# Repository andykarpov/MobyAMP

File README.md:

This project is a hobbyst DIY 2.1 amplifier based on TDA2030A and TDA1557Q chips.

The heart of the project is an arduino compatible custom board called "interface board" 
with atmega328 microcontroller and 16x2 (or 20x4) LCD panel, encoder, resistive keyboard and audio processor PT2322.
It is possible to make it even on a breadboard using a standard arduino and couple of wires :)

Some basic boards, such as interface board and amp boards contains both pcb design and electrical schematics.
All drawing (build/pdfs/pngs/etc) are already prepared to be printed on transarent sheets to make a final PCBs 
from the presensitized PCBs at home.

A few other things are not yet described (such as power board, connection between modules, etc, etc).
To be continued...

Custom eagle libraries are located under eagle_libraries folder.
To make a gerber / images from the command line you must have:
1. OSX (could work on other UNIX/Linux boxes)
2. eagle
3. homebrew
4. gerbv

Scripts should be changed to reflect a current Eagle installation path.

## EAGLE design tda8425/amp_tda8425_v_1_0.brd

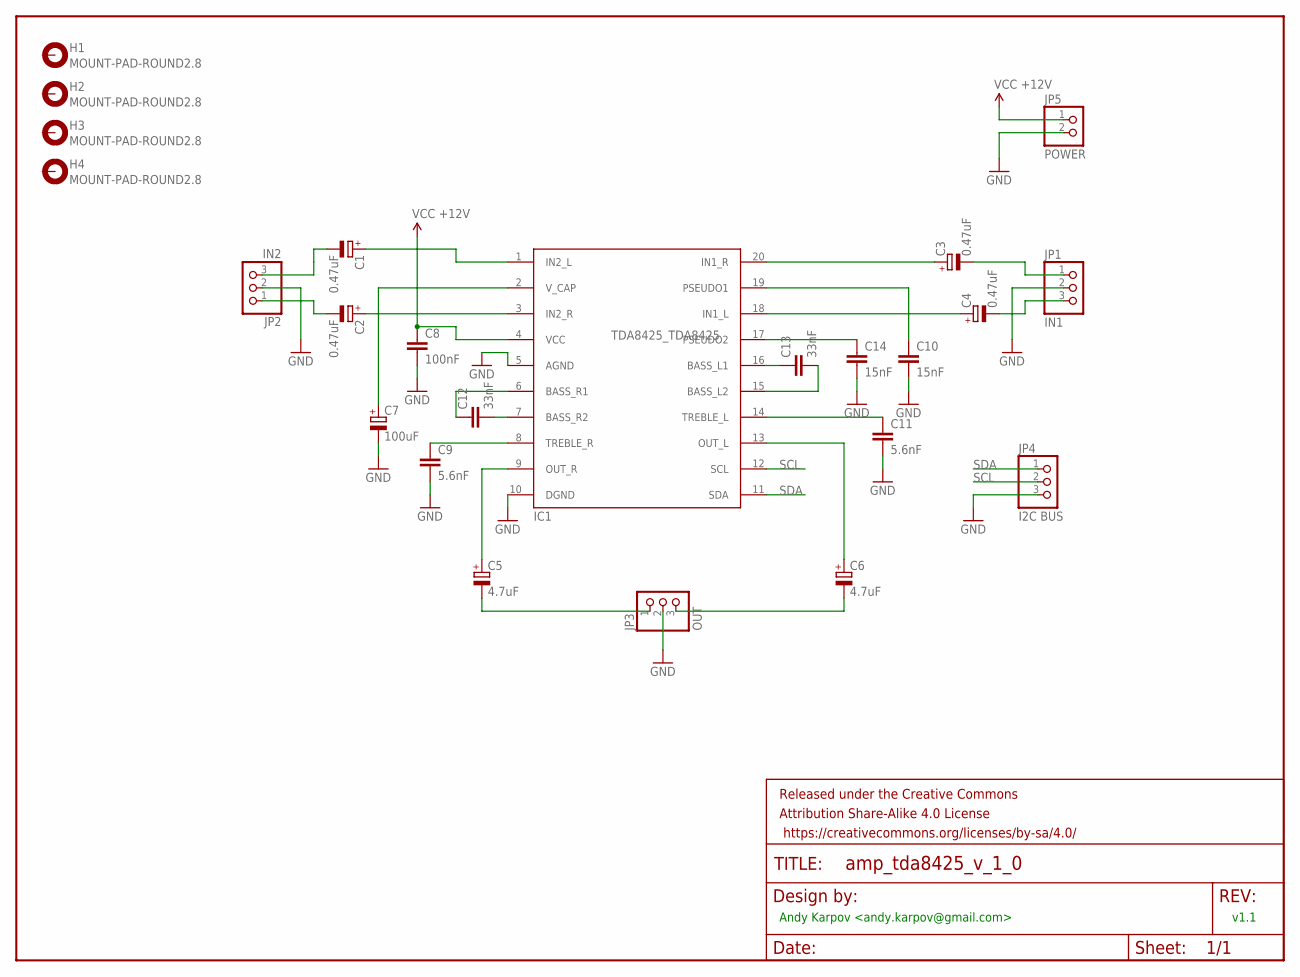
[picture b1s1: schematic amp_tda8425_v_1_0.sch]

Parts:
C1, C2, C3, C4: 0.47uF; E2,5-6
C5, C6: 4.7uF; E2,5-6
C7: 100uF; E2,5-6
C8: 100nF; C025-025X050
C9, C11: 5.6nF; C025-025X050
C10, C14: 15nF; C025-025X050
C12, C13: 33nF; C025-025X050
FRAME1: FRAME-LETTER; CREATIVE_COMMONS
H1, H2, H3, H4: MOUNT-PAD-ROUND2.8; 2,8-PAD
IC1: TDA8425_TDA8425; TDA8425_DIL20
JP1: IN1; 1X03
JP2: IN2; 1X03
JP3: OUT; 1X03
JP4: I2C BUS; 1X03
JP5: POWER; 1X02

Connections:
GND: C7.-, C8.2, C9.2, C10.2, C11.2, C14.2, IC1.5 (AGND), IC1.10 (DGND), JP1.2, JP2.2, JP3.2, JP4.3, JP5.2
unnamed: C1.+, IC1.1 (IN2_L)
unnamed: C1.-, JP2.3
unnamed: C2.+, IC1.3 (IN2_R)
unnamed: C2.-, JP2.1
unnamed: C3.+, IC1.20 (IN1_R)
unnamed: C4.+, IC1.18 (IN1_L)
unnamed: C3.-, JP1.1
unnamed: C4.-, JP1.3
unnamed: C7.+, IC1.2 (V_CAP)
unnamed: C12.1, IC1.6 (BASS_R1)
unnamed: C12.2, IC1.7 (BASS_R2)
unnamed: C9.1, IC1.8 (TREBLE_R)
unnamed: C5.+, IC1.9 (OUT_R)
unnamed: C5.-, JP3.1
unnamed: C6.+, IC1.13 (OUT_L)
unnamed: C6.-, JP3.3
unnamed: C13.1, IC1.16 (BASS_L1)
unnamed: C13.2, IC1.15 (BASS_L2)
unnamed: C14.1, IC1.17 (PSEUDO2)
unnamed: C11.1, IC1.14 (TREBLE_L)
unnamed: C10.1, IC1.19 (PSEUDO1)
SCL: IC1.12 (SCL), JP4.2
SDA: IC1.11 (SDA), JP4.1
VCC: C8.1, IC1.4 (VCC), JP5.1

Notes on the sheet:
Andy Karpov <andy.karpov@gmail.com>
v1.1

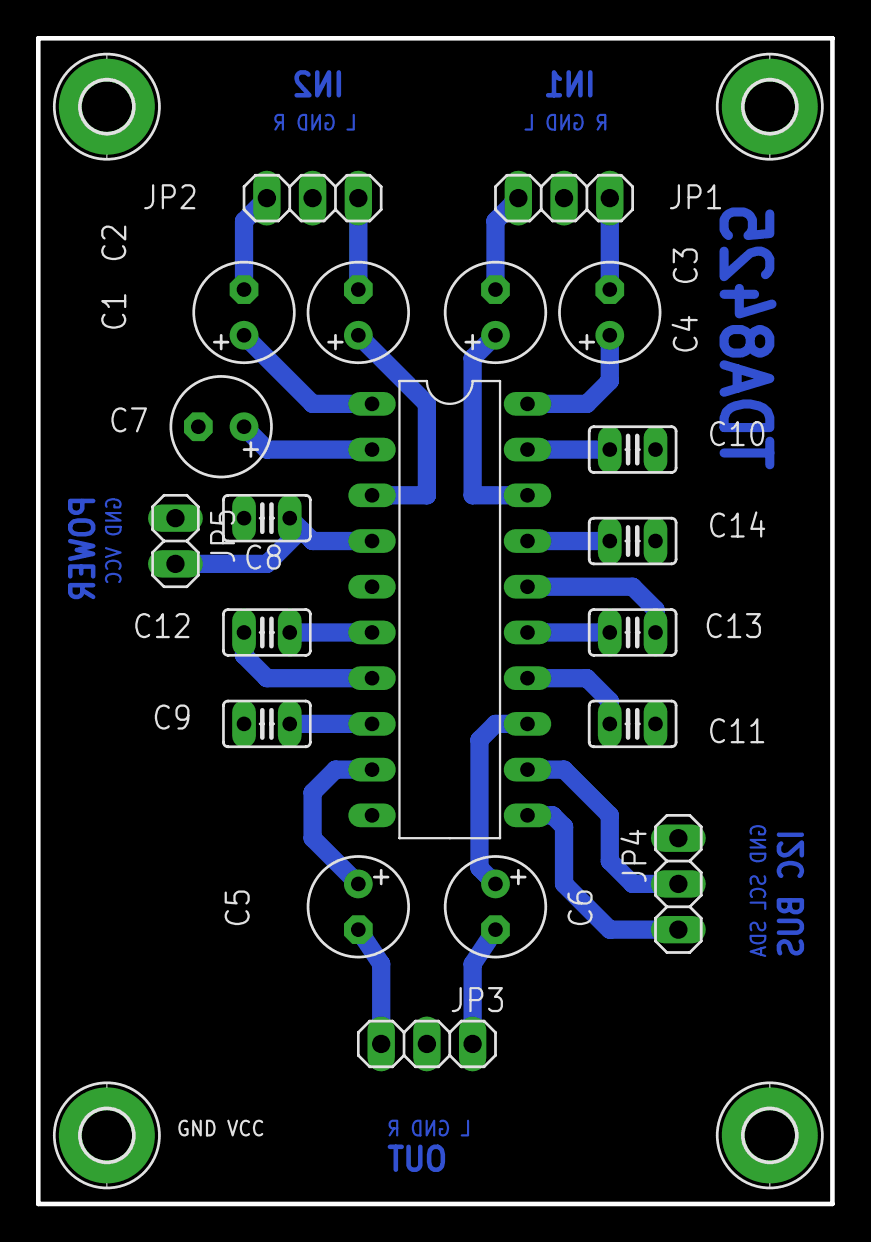
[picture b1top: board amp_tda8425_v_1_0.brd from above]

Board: 2 copper layers, 44.1 x 64.8 mm, 25 parts (0 on the bottom side), 25 nets.

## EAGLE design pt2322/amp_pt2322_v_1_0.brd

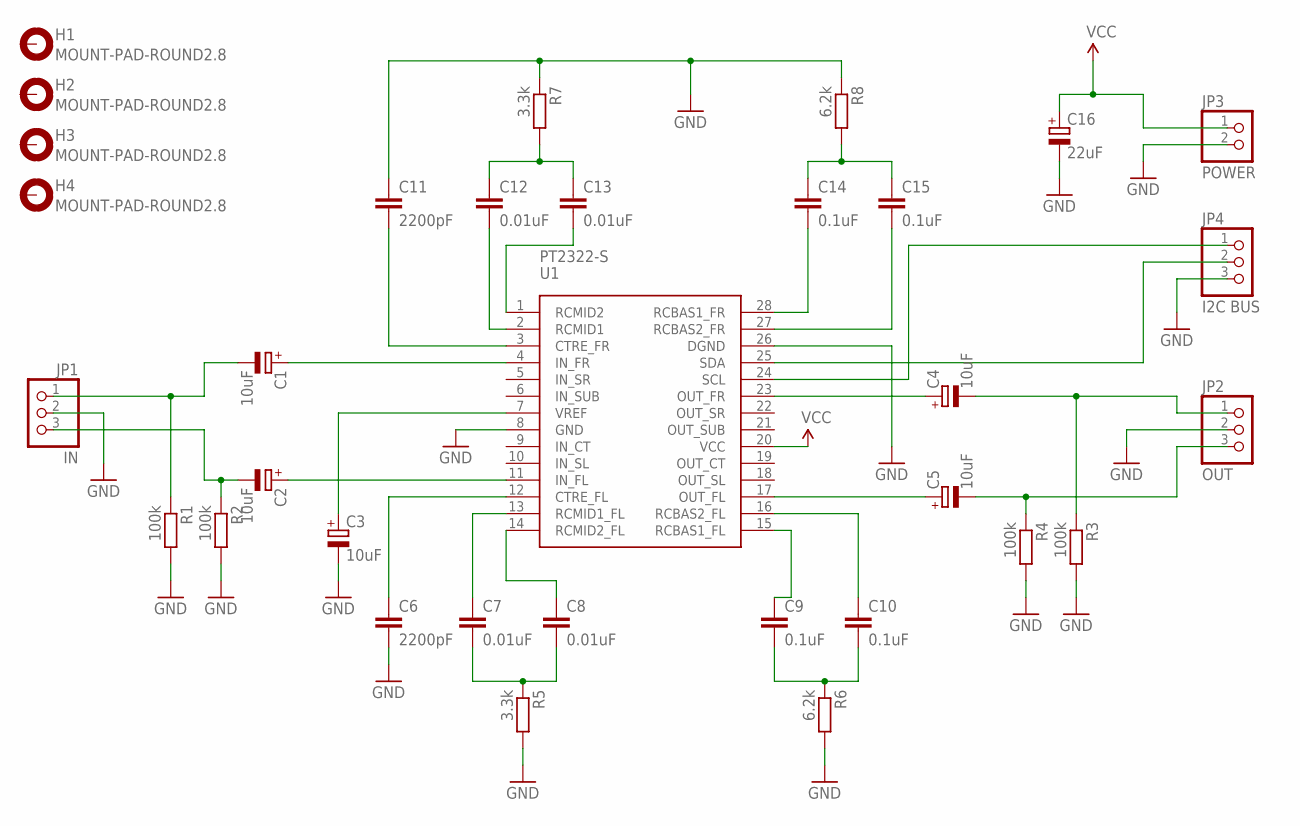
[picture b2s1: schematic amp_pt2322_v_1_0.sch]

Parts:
C1, C2, C3, C4, C5: 10uF; SMC_B
C6, C11: 2200pF; C0805K
C7, C8, C12, C13: 0.01uF; C0805K
C9, C10, C14, C15: 0.1uF; C0805K
C16: 22uF; SMC_B
H1, H2, H3, H4: MOUNT-PAD-ROUND2.8; 2,8-PAD
JP1: IN; 1X03
JP2: OUT; 1X03
JP3: POWER; 1X02
JP4: I2C BUS; 1X03
R1, R2, R3, R4: 100k; R0805
R5, R7: 3.3k; R0805
R6, R8: 6.2k; R0805
U1: PT2322-S; SOP28

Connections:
GND: C3.-, C6.2, C11.1, C16.-, JP1.2, JP2.2, JP3.2, JP4.3, R1.2, R2.2, R3.2, R4.2, R5.2, R6.2, R7.1, R8.1, U1.8 (GND), U1.26 (DGND)
unnamed: C1.+, U1.4 (IN_FR)
unnamed: C2.+, U1.11 (IN_FL)
unnamed: C1.-, JP1.1, R1.1
unnamed: C2.-, JP1.3, R2.1
unnamed: C3.+, U1.7 (VREF)
unnamed: C6.1, U1.12 (CTRE_FL)
unnamed: C7.1, U1.13 (RCMID1_FL)
unnamed: C8.1, U1.14 (RCMID2_FL)
unnamed: C7.2, C8.2, R5.1
unnamed: C10.1, U1.16 (RCBAS2_FL)
unnamed: C9.1, U1.15 (RCBAS1_FL)
unnamed: C9.2, C10.2, R6.1
unnamed: C13.2, U1.1 (RCMID2)
unnamed: C12.2, U1.2 (RCMID1)
unnamed: C11.2, U1.3 (CTRE_FR)
unnamed: C12.1, C13.1, R7.2
unnamed: C14.2, U1.28 (RCBAS1_FR)
unnamed: C15.2, U1.27 (RCBAS2_FR)
unnamed: C14.1, C15.1, R8.2
unnamed: C4.+, U1.23 (OUT_FR)
unnamed: C5.+, U1.17 (OUT_FL)
unnamed: C4.-, JP2.1, R3.1
unnamed: C5.-, JP2.3, R4.1
unnamed: JP4.1, U1.24 (SCL)
unnamed: JP4.2, U1.25 (SDA)
VCC: C16.+, JP3.1, U1.20 (VCC)

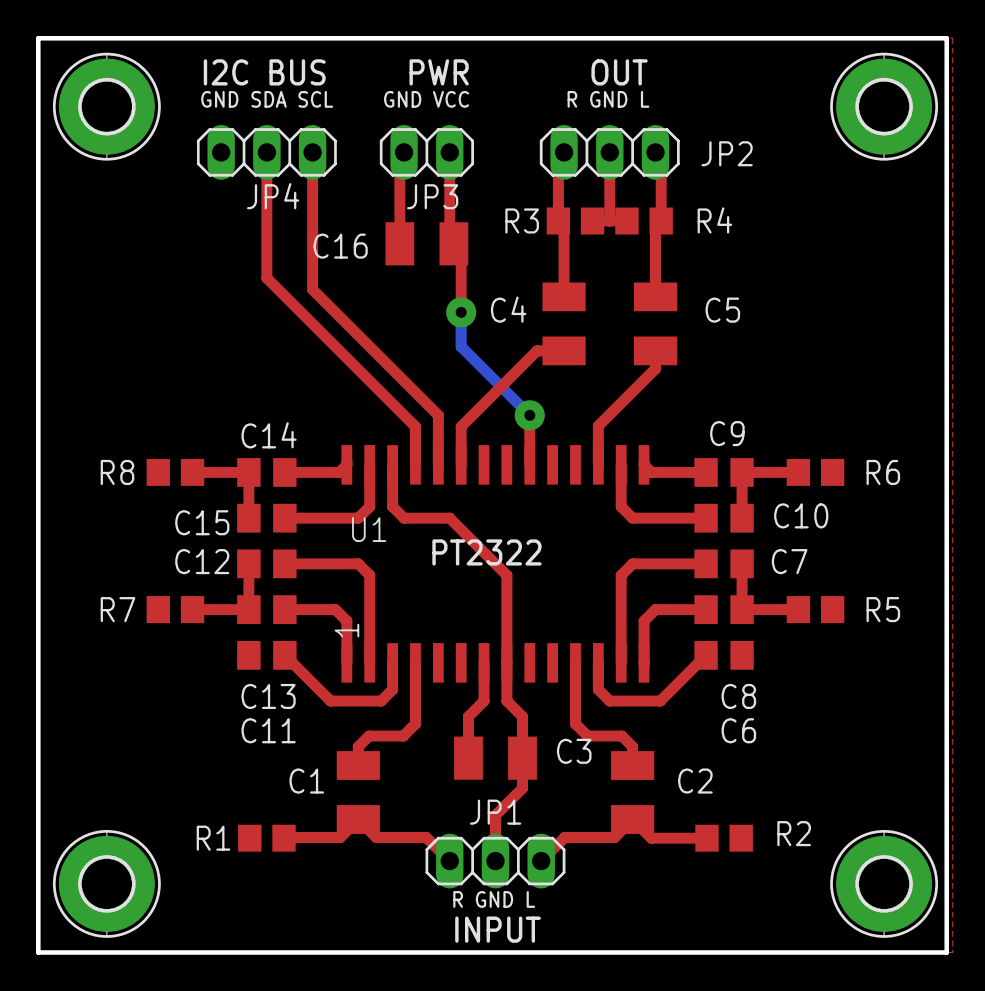
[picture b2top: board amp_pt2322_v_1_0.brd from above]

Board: 2 copper layers, 50.5 x 50.8 mm, 33 parts (0 on the bottom side), 27 nets.

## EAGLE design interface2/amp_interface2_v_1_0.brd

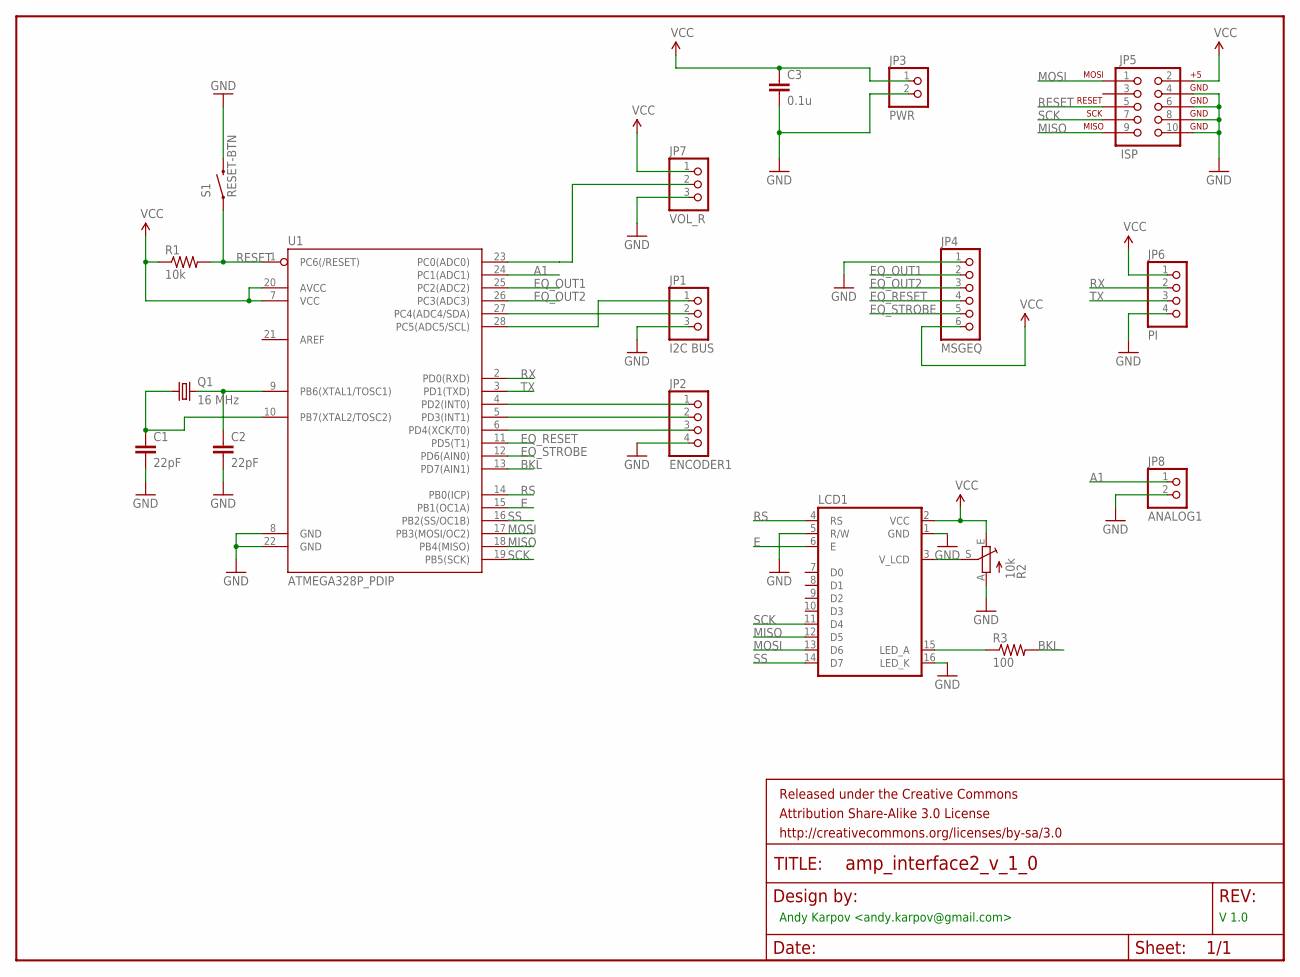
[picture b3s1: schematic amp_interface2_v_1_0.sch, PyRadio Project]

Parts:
C1, C2: 22pF; CAP-PTH-SMALL2
C3: 0.1u; CAP-PTH-SMALL2
FRAME1: FRAME-LETTER; CREATIVE_COMMONS
JP1: I2C BUS; 1X03
JP2: ENCODER1; 1X04
JP3: PWR; 1X02
JP4: MSGEQ; 1X06
JP5: ISP; 2X5-SHROUDED
JP6: PI; 1X04
JP7: VOL_R; 1X03
JP8: ANALOG1; 1X02
LCD1: LCD-4X20
Q1: 16 MHz; HC49/S
R1: 10k; AXIAL-0.4
R2: 10k; B64Y
R3: 100; AXIAL-0.5
S1: RESET-BTN; TACTILE-PTH
U1: ATMEGA328P_PDIP; DIL28-3

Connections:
A1: JP8.1, U1.24 (PC1(ADC1))
BKL: R3.P$2 (2), U1.13 (PD7(AIN1))
E: LCD1.6 (E), U1.15 (PB1(OC1A))
EQ_OUT1: JP4.2, U1.25 (PC2(ADC2))
EQ_OUT2: JP4.3, U1.26 (PC3(ADC3))
EQ_RESET: JP4.4, U1.11 (PD5(T1))
EQ_STROBE: JP4.5, U1.12 (PD6(AIN0))
GND: C1.2, C2.2, C3.2, JP1.3, JP2.4, JP3.2, JP4.1, JP5.4, JP5.6, JP5.8, JP5.10, JP6.4, JP7.3, JP8.2, LCD1.1 (GND), LCD1.5 (R/W), LCD1.16 (LED_K), R2.A, S1.3 (2), U1.8 (GND), U1.22 (GND)
MISO: JP5.9, LCD1.12 (D5), U1.18 (PB4(MISO))
MOSI: JP5.1, LCD1.13 (D6), U1.17 (PB3(MOSI/OC2))
unnamed: C2.1, Q1.2, U1.9 (PB6(XTAL1/TOSC1))
unnamed: C1.1, Q1.1, U1.10 (PB7(XTAL2/TOSC2))
unnamed: LCD1.3 (V_LCD), R2.S
unnamed: JP1.2, U1.27 (PC4(ADC4/SDA))
unnamed: JP1.1, U1.28 (PC5(ADC5/SCL))
unnamed: LCD1.15 (LED_A), R3.P$1 (1)
unnamed: JP2.3, U1.6 (PD4(XCK/T0))
unnamed: JP2.1, U1.4 (PD2(INT0))
unnamed: JP2.2, U1.5 (PD3(INT1))
PC0: JP7.2, U1.23 (PC0(ADC0))
RESET: JP5.5, R1.P$2 (2), S1.1, U1.1 (PC6(/RESET))
RS: LCD1.4 (RS), U1.14 (PB0(ICP))
RX: JP6.2, U1.2 (PD0(RXD))
SCK: JP5.7, LCD1.11 (D4), U1.19 (PB5(SCK))
SS: LCD1.14 (D7), U1.16 (PB2(SS/OC1B))
TX: JP6.3, U1.3 (PD1(TXD))
VCC: C3.1, JP3.1, JP4.6, JP5.2, JP6.1, JP7.1, LCD1.2 (VCC), R1.P$1 (1), R2.E, U1.7 (VCC), U1.20 (AVCC)

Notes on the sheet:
Andy Karpov <andy.karpov@gmail.com>
V 1.0

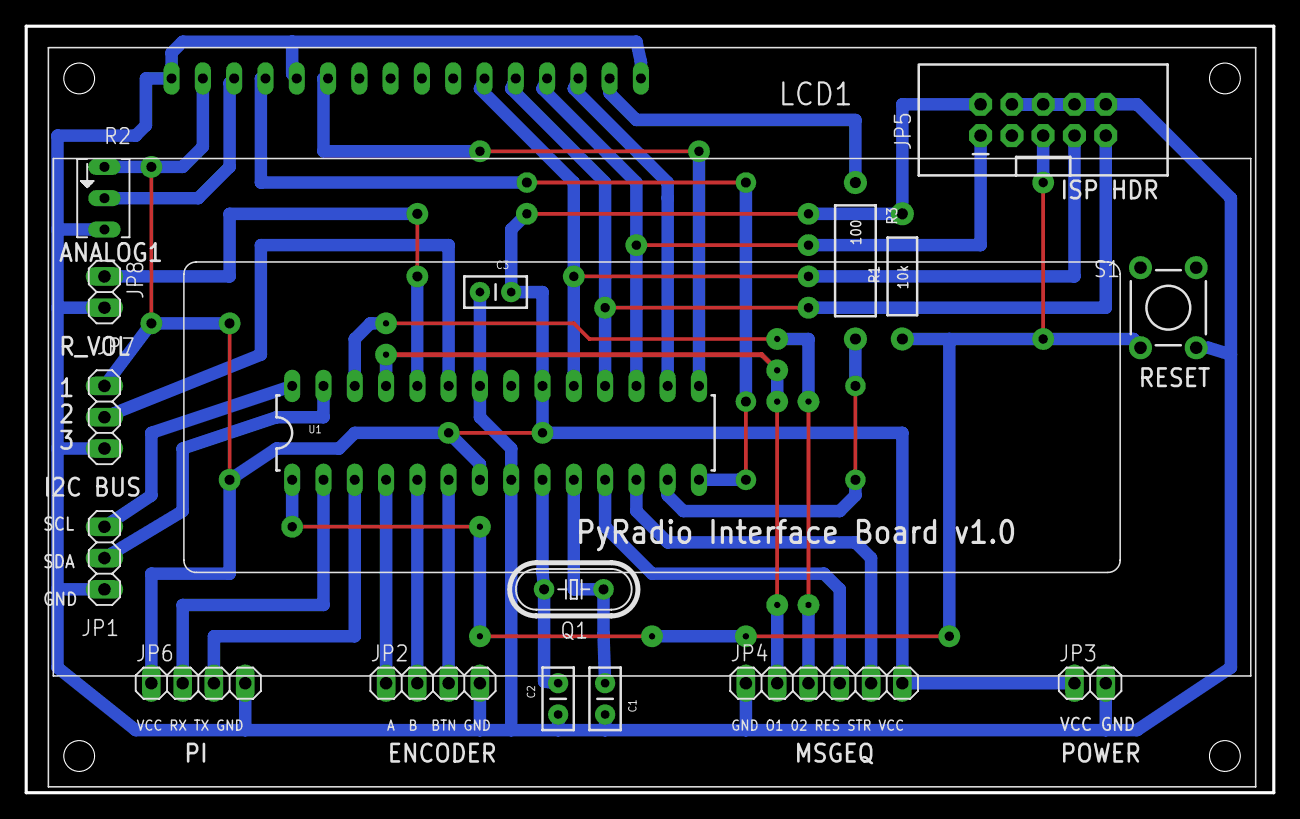
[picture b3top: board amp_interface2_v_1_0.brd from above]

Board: 2 copper layers, 101.3 x 62.2 mm, 19 parts (0 on the bottom side), 27 nets.

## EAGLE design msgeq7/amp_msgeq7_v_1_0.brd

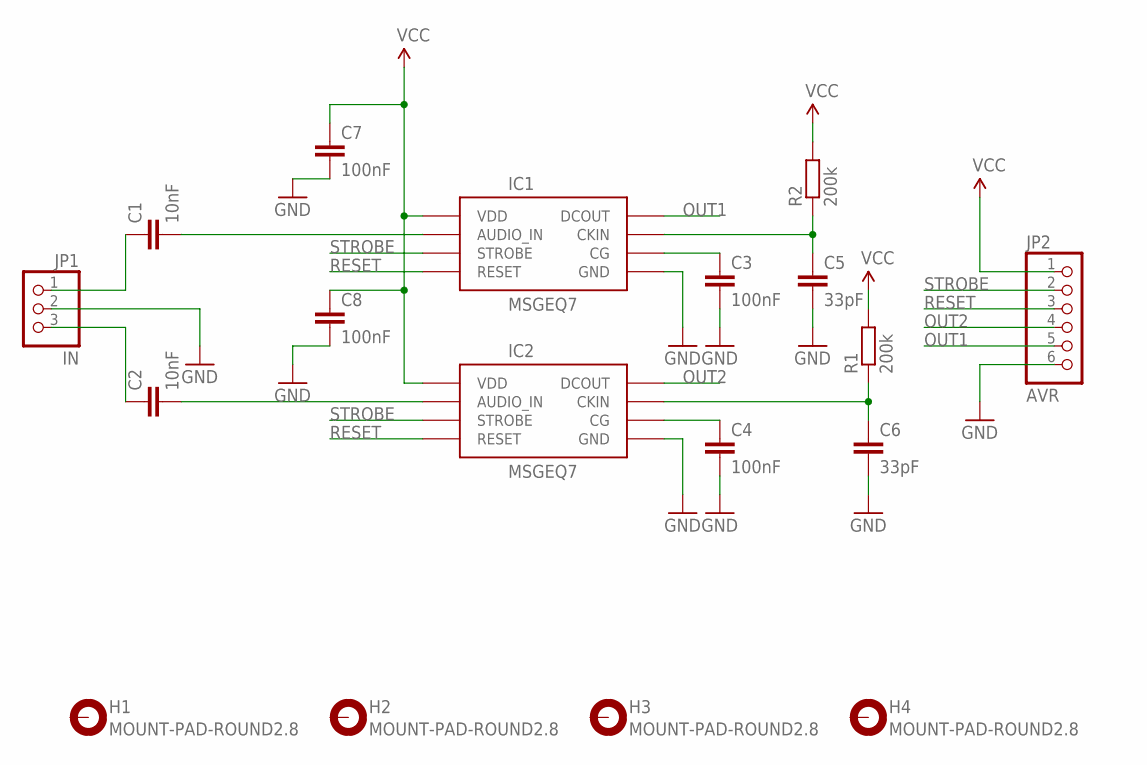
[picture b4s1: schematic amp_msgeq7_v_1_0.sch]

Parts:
C1, C2: 10nF; C025-030X050
C3, C4: 100nF; C025-030X050
C5, C6: 33pF; C025-030X050
C7, C8: 100nF; C025-025X050
H1, H2, H3, H4: MOUNT-PAD-ROUND2.8; 2,8-PAD
IC1, IC2: MSGEQ7DIP; DIL08
JP1: IN; 1X03
JP2: AVR; 1X06
R1, R2: 200k; 0204/7

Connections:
GND: C3.2, C4.2, C5.2, C6.2, C7.2, C8.2, IC1.2 (GND), IC2.2 (GND), JP1.2, JP2.6
unnamed: C1.1, JP1.1
unnamed: C1.2, IC1.5 (AUDIO_IN)
unnamed: C2.1, JP1.3
unnamed: C2.2, IC2.5 (AUDIO_IN)
unnamed: C3.1, IC1.6 (CG)
unnamed: C4.1, IC2.6 (CG)
unnamed: C5.1, IC1.8 (CKIN), R2.1
unnamed: C6.1, IC2.8 (CKIN), R1.1
OUT1: IC1.3 (DCOUT), JP2.5
OUT2: IC2.3 (DCOUT), JP2.4
RESET: IC1.7 (RESET), IC2.7 (RESET), JP2.3
STROBE: IC1.4 (STROBE), IC2.4 (STROBE), JP2.2
VCC: C7.1, C8.1, IC1.1 (VDD), IC2.1 (VDD), JP2.1, R1.2, R2.2

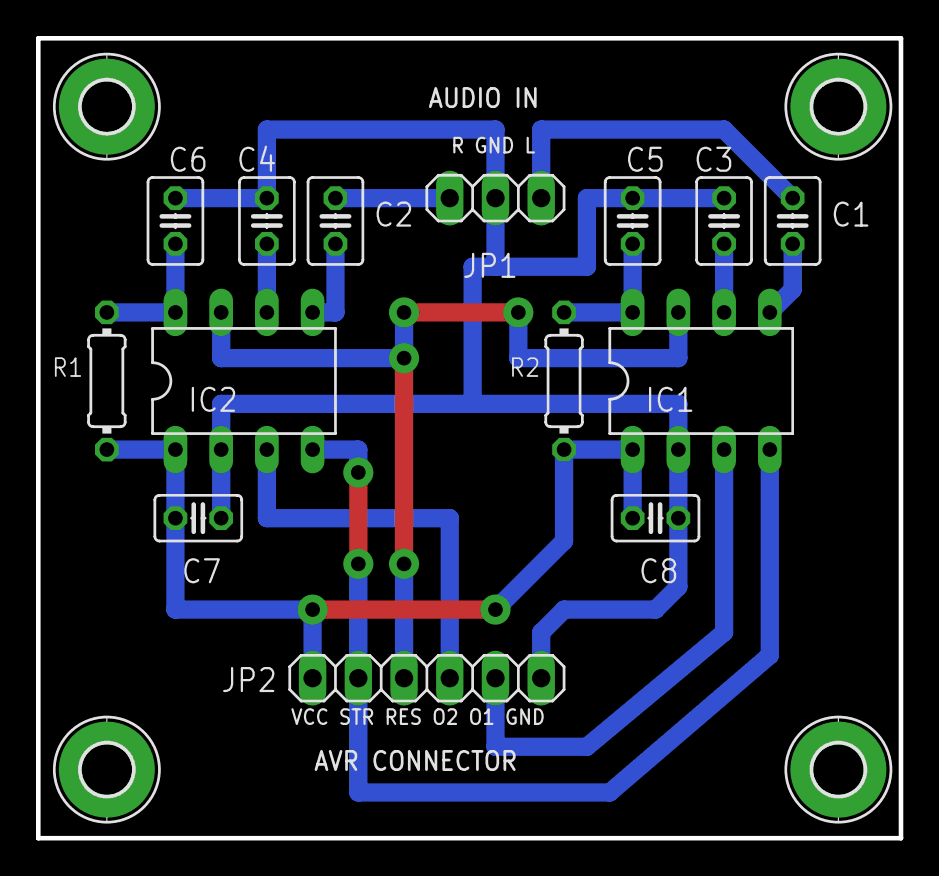
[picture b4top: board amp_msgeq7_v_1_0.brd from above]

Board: 2 copper layers, 47.9 x 44.4 mm, 18 parts (0 on the bottom side), 14 nets.

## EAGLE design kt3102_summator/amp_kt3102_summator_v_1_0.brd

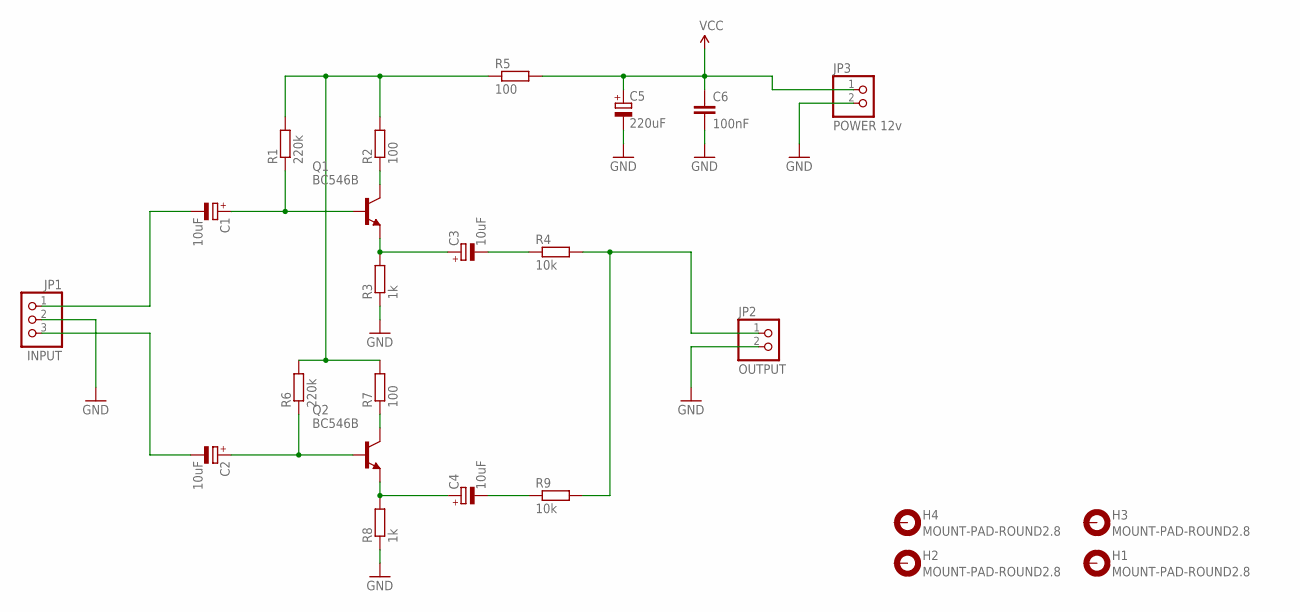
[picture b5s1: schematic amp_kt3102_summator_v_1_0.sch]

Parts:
C1, C2, C3, C4: 10uF; E2,5-5
C5: 220uF; E3,5-8
C6: 100nF; C050-025X075
H1, H2, H3, H4: MOUNT-PAD-ROUND2.8; 2,8-PAD
JP1: INPUT; 1X03
JP2: OUTPUT; 1X02
JP3: POWER 12v; 1X02
Q1, Q2: BC546B; TO92-EBC
R1, R6: 220k; 0204/7
R2, R5, R7: 100; 0204/7
R3, R8: 1k; 0204/7
R4, R9: 10k; 0204/7

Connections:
GND: C5.-, C6.2, JP1.2, JP2.2, JP3.2, R3.1, R8.1
unnamed: C1.-, JP1.1
unnamed: C1.+, Q1.B, R1.1
unnamed: Q1.C, R2.1
unnamed: R1.2, R2.2, R5.1, R6.2, R7.2
unnamed: C3.+, Q1.E, R3.2
unnamed: C3.-, R4.1
unnamed: JP2.1, R4.2, R9.2
unnamed: Q2.C, R7.1
unnamed: C2.+, Q2.B, R6.1
unnamed: C2.-, JP1.3
unnamed: C4.+, Q2.E, R8.2
unnamed: C4.-, R9.1
VCC: C5.+, C6.1, JP3.1, R5.2

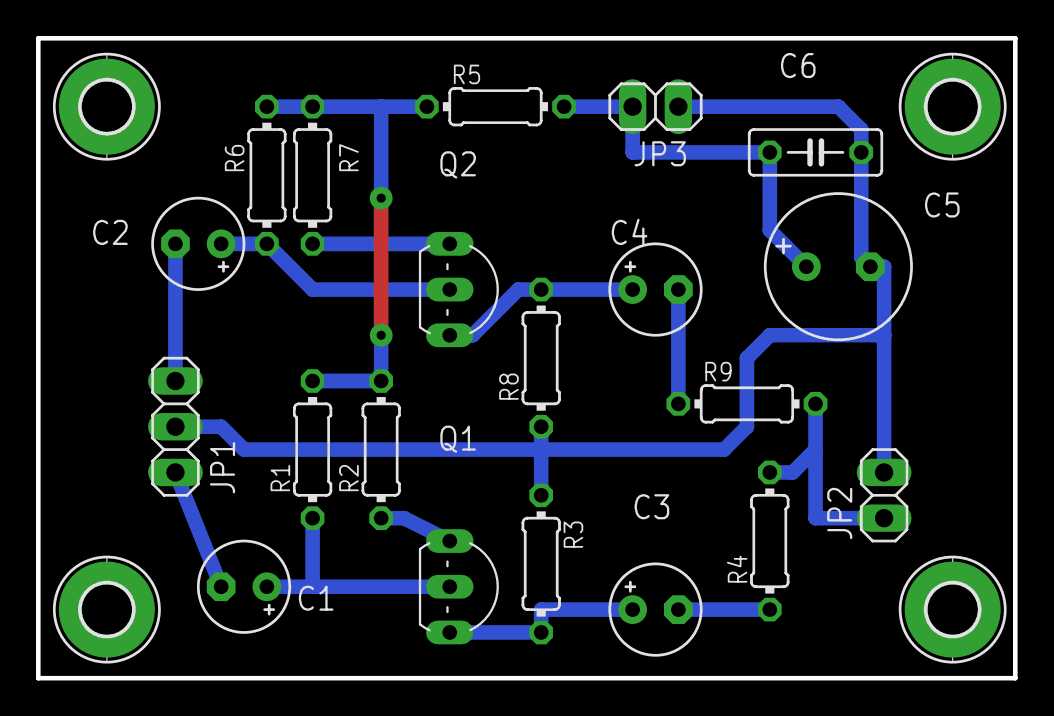
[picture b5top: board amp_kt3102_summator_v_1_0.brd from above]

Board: 2 copper layers, 54.3 x 35.5 mm, 24 parts (0 on the bottom side), 14 nets.

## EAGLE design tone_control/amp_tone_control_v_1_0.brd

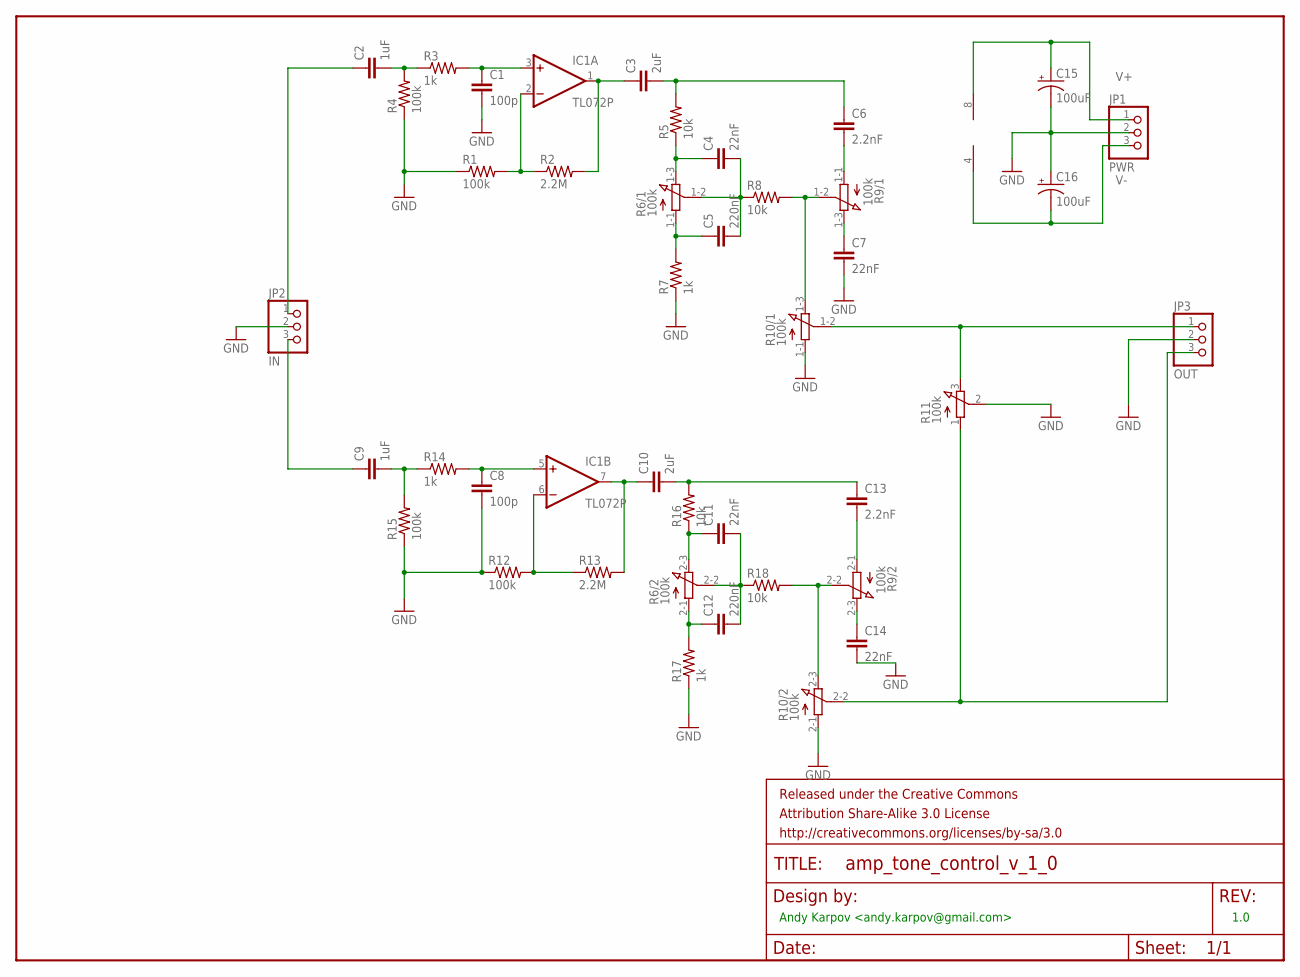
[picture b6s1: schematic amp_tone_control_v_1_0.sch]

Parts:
C1, C8: 100p; CAP-PTH-5MM
C2, C9: 1uF; CAP-PTH-LARGE
C3, C10: 2uF; CAP-PTH-LARGE
C4, C11: 22nF; CAP-PTH-5MM
C5, C12: 220nF; CAP-PTH-5MM
C6, C13: 2.2nF; CAP-PTH-5MM
C7, C14: 22nF; CAP-PTH-LARGE
C15, C16: 100uF; CPOL-RADIAL-100UF-25V
FRAME1: FRAME-LETTER; CREATIVE_COMMONS
IC1: TL072P; DIL08
JP1: PWR; 1X03
JP2: IN; 1X03
JP3: OUT; 1X03
R1, R4, R12, R15: 100k; AXIAL-0.4
R2, R13: 2.2M; AXIAL-0.4
R3, R7, R14, R17: 1k; AXIAL-0.4
R5, R8, R16, R18: 10k; AXIAL-0.4
R6, R9, R10: 100k; 3RP/1610G
R11: 100k; 3RP/1610N

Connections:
GND: C1.2, C7.2, C8.2, C14.2, C15.2 (-), C16.1 (+), JP1.2, JP2.2, JP3.2, R1.P$1 (1), R4.P$1 (1), R7.P$1 (1), R10.1-1 (A), R10.2-1 (A), R11.2 (S), R12.P$1 (1), R15.P$1 (1), R17.P$1 (1)
unnamed: IC1.2 (-IN), R1.P$2 (2), R2.P$1 (1)
unnamed: C3.1, IC1.1 (OUT), R2.P$2 (2)
unnamed: C2.2, R3.P$1 (1), R4.P$2 (2)
unnamed: C1.1, IC1.3 (+IN), R3.P$2 (2)
unnamed: C9.1, JP2.3
unnamed: C5.1, R6.1-1 (A), R7.P$2 (2)
unnamed: R8.P$2 (2), R9.1-2 (S), R10.1-3 (E)
unnamed: C6.2, R9.1-1 (A)
unnamed: C7.1, R9.1-3 (E)
unnamed: JP3.1, R10.1-2 (S), R11.3 (E)
unnamed: C2.1, JP2.1
unnamed: C9.2, R14.P$1 (1), R15.P$2 (2)
unnamed: C12.1, R6.2-1 (A), R17.P$2 (2)
unnamed: C8.1, IC1.5 (+IN), R14.P$2 (2)
unnamed: IC1.6 (-IN), R12.P$2 (2), R13.P$1 (1)
unnamed: C10.1, IC1.7 (OUT), R13.P$2 (2)
unnamed: C10.2, C13.1, R16.P$2 (2)
unnamed: C13.2, R9.2-1 (A)
unnamed: C11.1, R6.2-3 (E), R16.P$1 (1)
unnamed: C14.1, R9.2-3 (E)
unnamed: C11.2, C12.2, R6.2-2 (S), R18.P$1 (1)
unnamed: C4.2, C5.2, R6.1-2 (S), R8.P$1 (1)
unnamed: C4.1, R5.P$1 (1), R6.1-3 (E)
unnamed: C3.2, C6.1, R5.P$2 (2)
unnamed: R9.2-2 (S), R10.2-3 (E), R18.P$2 (2)
unnamed: JP3.3, R10.2-2 (S), R11.1 (A)
V+: C15.1 (+), IC1.8 (V+), JP1.1
V-: C16.2 (-), IC1.4 (V-), JP1.3

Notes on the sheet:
Andy Karpov <andy.karpov@gmail.com>
1.0

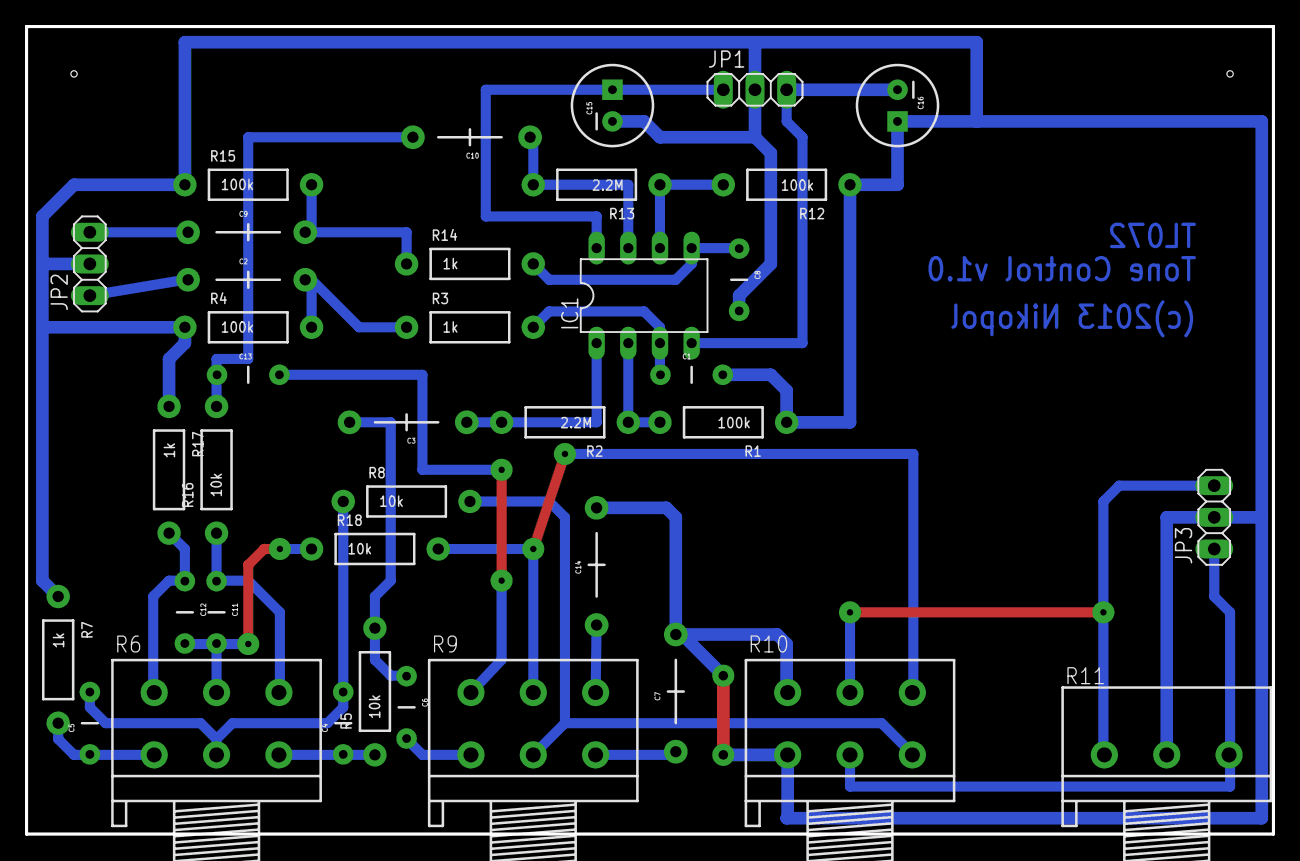
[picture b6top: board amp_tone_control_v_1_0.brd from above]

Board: 2 copper layers, 100.0 x 64.8 mm, 39 parts (0 on the bottom side), 29 nets.

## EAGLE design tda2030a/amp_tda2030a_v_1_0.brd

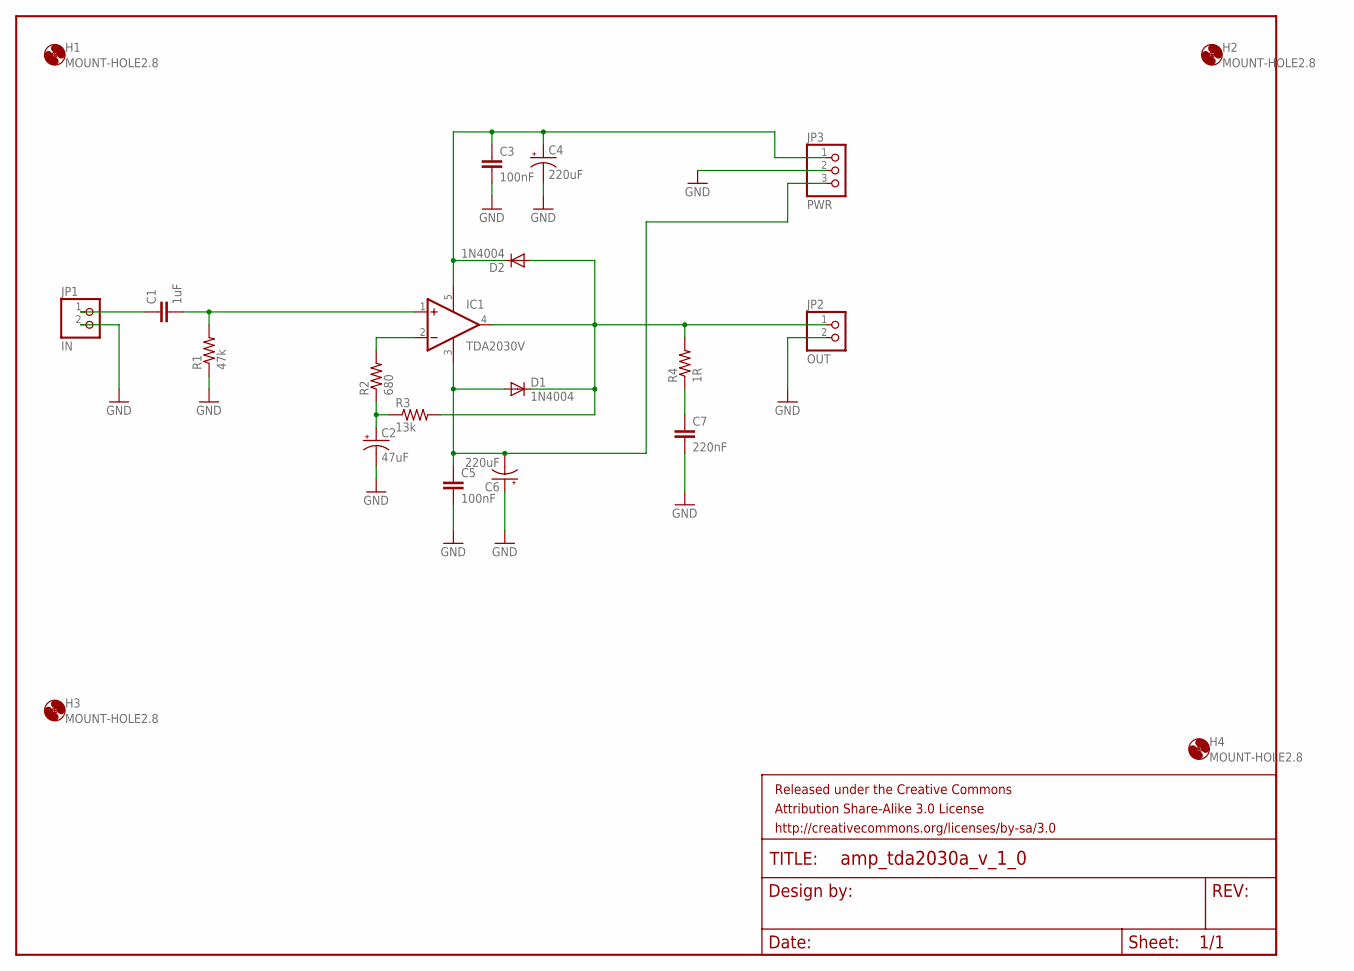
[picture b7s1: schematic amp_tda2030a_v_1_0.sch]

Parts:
C1: 1uF; CAP-PTH-LARGE
C2: 47uF; CPOL-RADIAL-100UF-25V
C3, C5: 100nF; CAP-PTH-5MM
C4, C6: 220uF; CPOL-RADIAL-100UF-25V
C7: 220nF; CAP-PTH-LARGE
D1, D2: 1N4004; DO41-10
FRAME1: FRAME-LETTER; CREATIVE_COMMONS
H1, H2, H3, H4: MOUNT-HOLE2.8; 2,8
IC1: TDA2030V; CB360
JP1: IN; 1X02
JP2: OUT; 1X02
JP3: PWR; 1X03
R1: 47k; AXIAL-0.4
R2: 680; AXIAL-0.4
R3: 13k; AXIAL-0.4
R4: 1R; AXIAL-0.4

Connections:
GND: C2.2 (-), C3.2, C4.2 (-), C5.2, C6.1 (+), C7.2, JP1.2, JP2.2, JP3.2, R1.P$1 (1)
unnamed: C1.1, JP1.1
unnamed: C1.2, IC1.1 (+IN), R1.P$2 (2)
unnamed: IC1.2 (-IN), R2.P$2 (2)
unnamed: C2.1 (+), R2.P$1 (1), R3.P$1 (1)
unnamed: C5.1, C6.2 (-), D1.A, IC1.3 (GND), JP3.3
unnamed: D1.C, D2.A, IC1.4 (OUT), JP2.1, R3.P$2 (2), R4.P$2 (2)
unnamed: C7.1, R4.P$1 (1)
unnamed: C3.1, C4.1 (+), D2.C, IC1.5 (V+), JP3.1

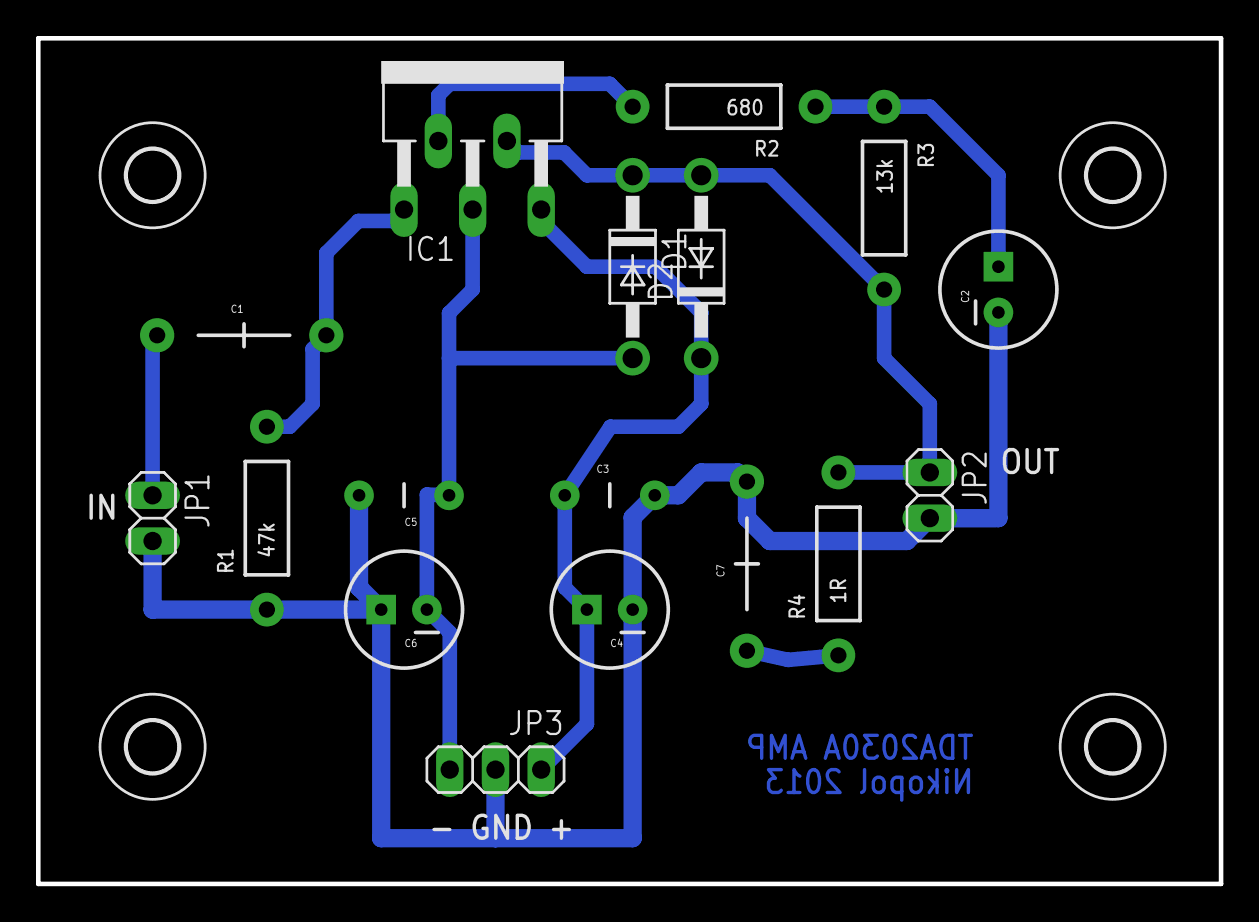
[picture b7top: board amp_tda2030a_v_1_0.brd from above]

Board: 2 copper layers, 65.7 x 47.0 mm, 22 parts (0 on the bottom side), 9 nets.

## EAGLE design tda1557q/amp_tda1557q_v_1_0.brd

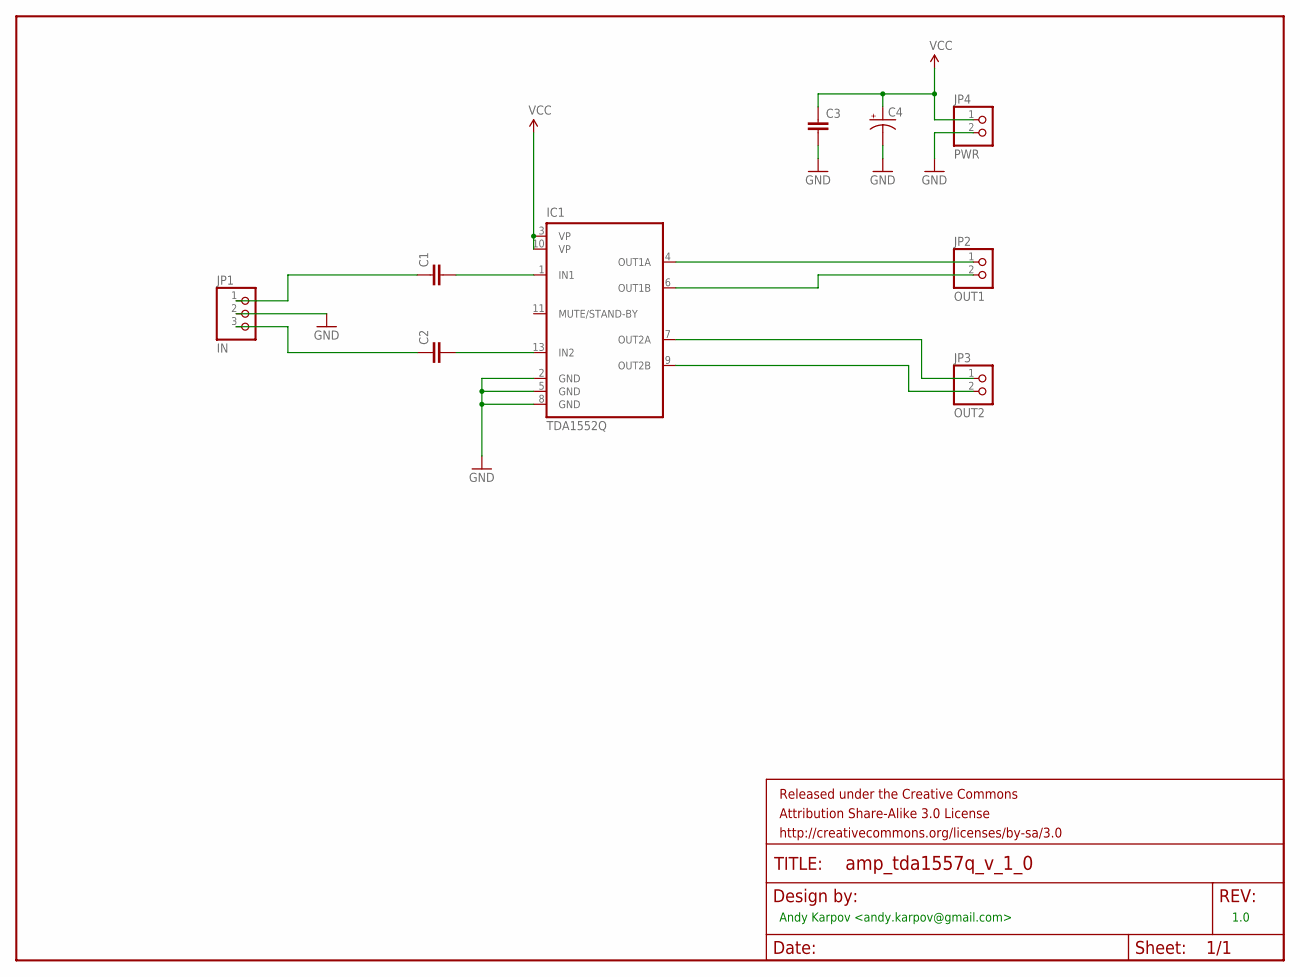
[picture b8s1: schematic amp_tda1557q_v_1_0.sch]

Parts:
C1, C2, C3: CAPPTH3; CAP-PTH-LARGE
C4: CAP_POLPTH3; CPOL-RADIAL-1000UF-63V
FRAME1: FRAME-LETTER; CREATIVE_COMMONS
IC1: TDA1552Q; MULTIWAT-SIL13
JP1: IN; 1X03
JP2: OUT1; 1X02
JP3: OUT2; 1X02
JP4: PWR; 1X02

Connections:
GND: C3.2, C4.2 (-), IC1.2 (GND), IC1.5 (GND), IC1.8 (GND), JP1.2, JP4.2
unnamed: C1.1, JP1.1
unnamed: C1.2, IC1.1 (IN1)
unnamed: C2.1, JP1.3
unnamed: C2.2, IC1.13 (IN2)
unnamed: IC1.4 (OUT1A), JP2.1
unnamed: IC1.6 (OUT1B), JP2.2
unnamed: IC1.7 (OUT2A), JP3.1
unnamed: IC1.9 (OUT2B), JP3.2
VCC: C3.1, C4.1 (+), IC1.3 (VP), IC1.10 (VP), JP4.1

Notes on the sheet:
Andy Karpov <andy.karpov@gmail.com>
1.0

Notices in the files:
tone_control/amp_tone_control_v_1_0.brd:
(c)2013 Nikopol
parts and their libraries:
SparkFun-DigitalIC: Licensing: CC v3.0 Share-Alike You are welcome to use this library for commercial purposes.
SparkFun-Aesthetics: Released under the Creative Commons Attribution Share-Alike 3.0 License
SparkFun-Aesthetics: http://creativecommons.org/licenses/by-sa/3.0
